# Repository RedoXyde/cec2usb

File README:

CEC to USB adapter, with HDMI passthrough

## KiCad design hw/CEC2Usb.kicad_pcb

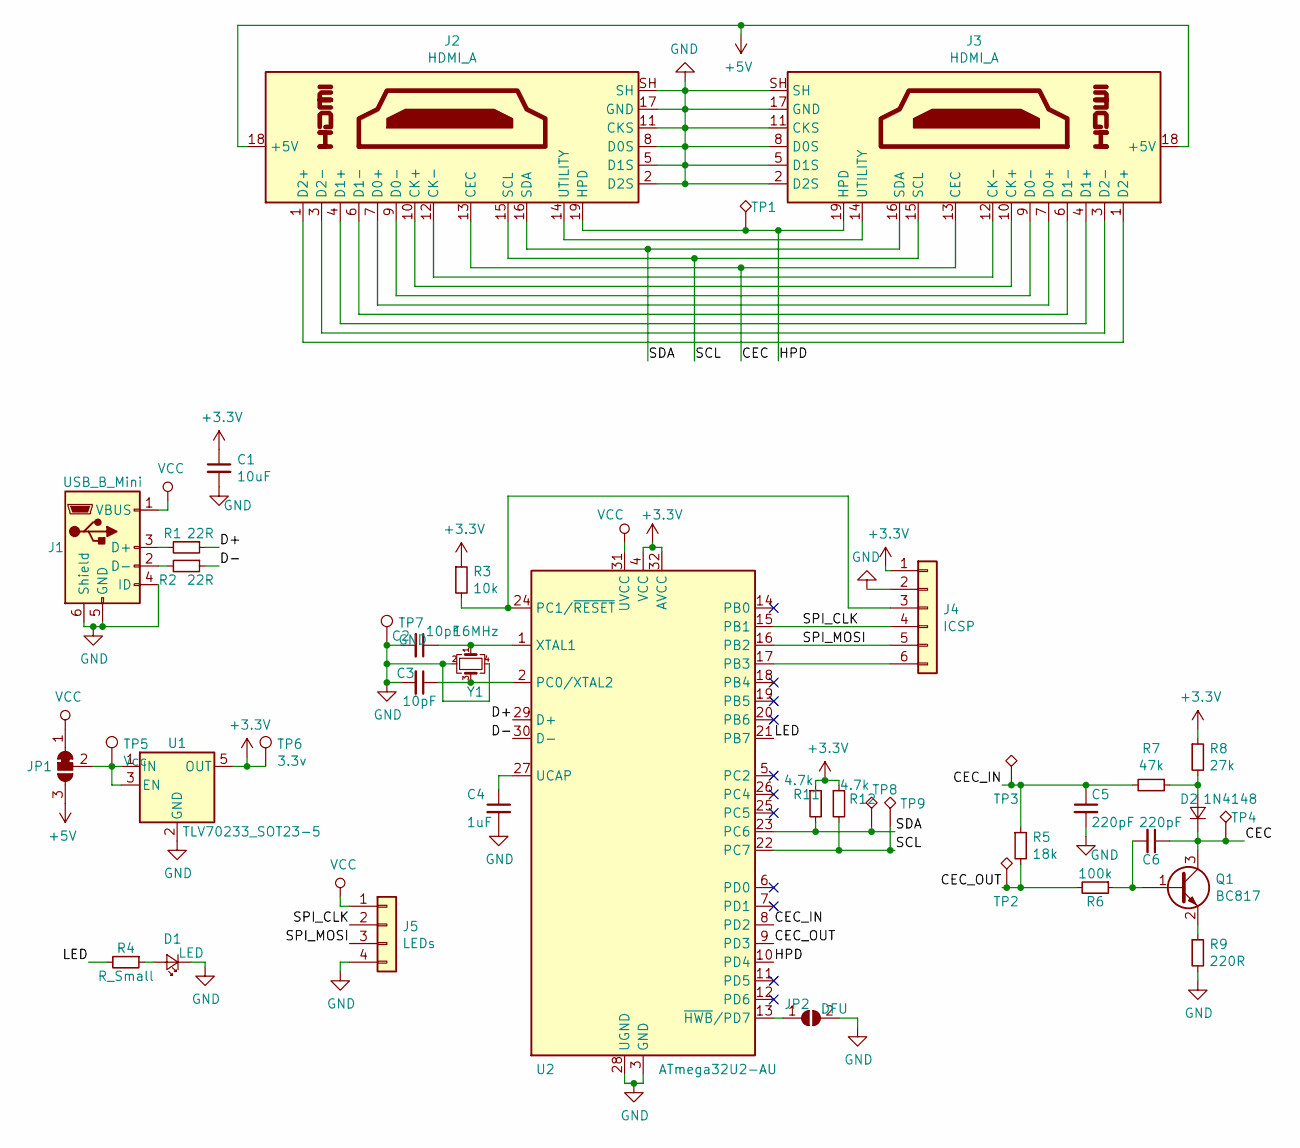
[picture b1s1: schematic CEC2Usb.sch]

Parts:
C1: 10uF; C_0603_1608Metric
C2, C3: 10pF; C_0603_1608Metric
C4: 1uF; C_0603_1608Metric
C5, C6: 220pF; C_0603_1608Metric
D1: LED; LED_0603_1608Metric_Pad1.05x0.95mm_HandSolder
D2: 1N4148; D_SOD-123
J1: USB_B_Mini; USB_Mini-B_Lumberg_2486_01_Horizontal
J2: HDMI_A; HDMI-19P-SND13x
J3: HDMI_A; HDMI-19P-SNDx
J4: ICSP; PinHeader_1x06_P1.27mm_Vertical
J5: LEDs; PinHeader_1x04_P2.54mm_Vertical
JP1: SolderJumper_3_Bridged12; SolderJumper-3_P1.3mm_Bridged12_RoundedPad1.0x1.5mm
JP2: DFU; SolderJumper-2_P1.3mm_Open_RoundedPad1.0x1.5mm
Q1: BC817; SOT-23
R1, R2: 22R; R_0603_1608Metric_Pad1.05x0.95mm_HandSolder
R3: 10k; R_0603_1608Metric_Pad1.05x0.95mm_HandSolder
R4: R_Small; R_0603_1608Metric_Pad1.05x0.95mm_HandSolder
R5: 18k; R_0603_1608Metric_Pad1.05x0.95mm_HandSolder
R6: 100k; R_0603_1608Metric_Pad1.05x0.95mm_HandSolder
R7: 47k; R_0603_1608Metric_Pad1.05x0.95mm_HandSolder
R8: 27k; R_0603_1608Metric_Pad1.05x0.95mm_HandSolder
R9: 220R; R_0603_1608Metric_Pad1.05x0.95mm_HandSolder
R11, R12: 4.7k; R_0603_1608Metric_Pad1.05x0.95mm_HandSolder
TP1: HPD; TestPoint_Pad_1.5x1.5mm
TP2: CEC_OUT; TestPoint_Pad_1.5x1.5mm
TP3: CEC_IN; TestPoint_Pad_1.5x1.5mm
TP4: CEC; TestPoint_Pad_1.5x1.5mm
TP5: Vcc; TestPoint_Pad_1.5x1.5mm
TP6: 3.3v; TestPoint_Pad_1.5x1.5mm
TP7: GND; TestPoint_Pad_1.5x1.5mm
TP8: SDA; TestPoint_Pad_1.5x1.5mm
TP9: SCL; TestPoint_Pad_1.5x1.5mm
U1: TLV70233_SOT23-5; SOT-23-5
U2: ATmega32U2-AU; TQFP-32_7x7mm_P0.8mm
Y1: 16MHz; Crystal_SMD_3225-4Pin_3.2x2.5mm

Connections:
+3V3: C1.1, J4.1, R3.1, R8.1, R11.1, R12.1, TP6.1, U1.5 (OUT), U2.4 (VCC), U2.32 (AVCC)
+5V: J2.18 (+5V), J3.18 (+5V), JP1.3 (B); also elsewhere on the board
/CEC: C6.1, D2.1 (K), J2.13 (CEC), J3.13 (CEC), Q1.3 (C), TP4.1
/CEC_IN: C5.1, R5.1, R7.2, TP3.1, U2.8 (PD2)
/CEC_OUT: R5.2, R6.2, TP2.1, U2.9 (PD3)
/D+: R1.1, U2.29 (D+)
/D-: R2.1, U2.30 (D-)
/HPD: J2.19 (HPD), J3.19 (HPD), TP1.1, U2.10 (PD4)
/LED: R4.2, U2.21 (PB7)
/SCL: J2.15 (SCL), J3.15 (SCL), R12.2, TP9.1, U2.22 (PC7)
/SDA: J2.16 (SDA), J3.16 (SDA), R11.2, TP8.1, U2.23 (PC6)
/SPI_CLK: J4.4, J5.2, U2.15 (PB1); also elsewhere on the board
/SPI_MOSI: J4.5, J5.3, U2.16 (PB2); also elsewhere on the board
GND: C1.2, C2.2, C3.2, C4.2, C5.2, D1.1 (K), J1.4 (ID), J1.5 (GND), J1.6 (Shield), J2.2 (D2S), J2.5 (D1S), J2.8 (D0S), J2.11 (CKS), J2.17 (GND), J2.SH, J3.2 (D2S), J3.5 (D1S), J3.8 (D0S), J3.11 (CKS), J3.17 (GND), J3.SH, J4.2, J5.4, JP2.2 (B), R9.2, TP7.1, U1.2 (GND), U2.3 (GND), U2.28 (UGND), Y1.2, Y1.4; also elsewhere on the board
unnamed: C2.1, U2.1 (XTAL1), Y1.1
unnamed: C3.1, U2.2 (PC0/XTAL2), Y1.3
unnamed: C4.1, U2.27 (UCAP)
unnamed: C6.2, Q1.1 (B), R6.1
unnamed: D1.2 (A), R4.1
unnamed: D2.2 (A), R7.1, R8.2
unnamed: J1.2 (D-), R2.2
unnamed: J1.3 (D+), R1.2
unnamed: J2.1 (D2+), J3.1 (D2+)
unnamed: J2.3 (D2-), J3.3 (D2-)
unnamed: J2.4 (D1+), J3.4 (D1+)
unnamed: J2.6 (D1-), J3.6 (D1-)
unnamed: J2.7 (D0+), J3.7 (D0+)
unnamed: J2.9 (D0-), J3.9 (D0-)
unnamed: J2.10 (CK+), J3.10 (CK+)
unnamed: J2.12 (CK-), J3.12 (CK-)
unnamed: J2.14 (UTILITY), J3.14 (UTILITY)
unnamed 31: J4.3, R3.2, U2.24 (PC1/~RESET); also elsewhere on the board
unnamed: J4.6, U2.17 (PB3)
unnamed 33: JP1.2 (C), TP5.1, U1.1 (IN), U1.3 (EN); also elsewhere on the board
unnamed: JP2.1 (A), U2.13 (~HWB~/PD7)
unnamed: Q1.2 (E), R9.1
VCC: J1.1 (VBUS), J5.1, JP1.1 (A), U2.31 (UVCC); also elsewhere on the board

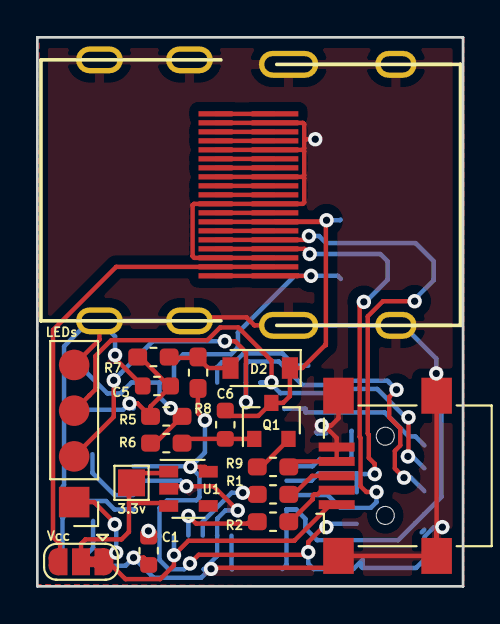
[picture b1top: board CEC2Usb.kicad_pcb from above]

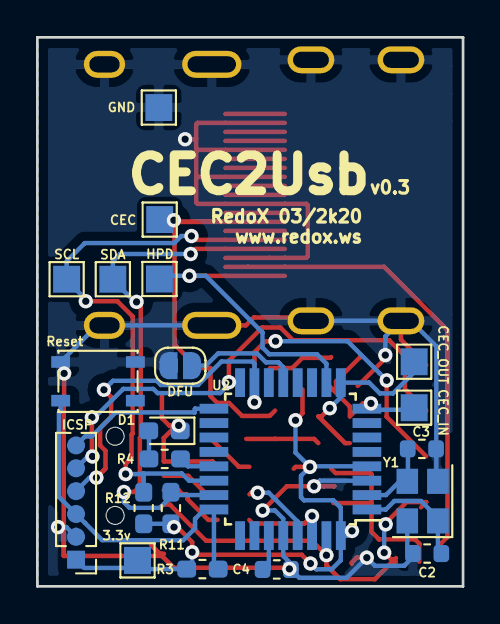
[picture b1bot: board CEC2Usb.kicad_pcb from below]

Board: 2 copper layers, 23.7 x 30.5 mm, 40 parts (21 on the bottom side), 37 nets.

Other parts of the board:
3.3v: Vcc; TestPoint_Pad_1.5x1.5mm
LEDs: LEDs; PinHeader_1x04_P2.54mm_Vertical
Reset: SW_SPST_PTS810
Vcc: SolderJumper_3_Bridged12; SolderJumper-3_P1.3mm_Bridged12_RoundedPad1.0x1.5mm

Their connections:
+5V: Vcc.3; also elsewhere on the board
/SPI_CLK: LEDs.2; also elsewhere on the board
/SPI_MOSI: LEDs.3; also elsewhere on the board
GND: LEDs.4, Reset.2; also elsewhere on the board
unnamed 31: Reset.1; also elsewhere on the board
unnamed 33: 3.3v.1, Vcc.2; also elsewhere on the board
VCC: LEDs.1, Vcc.1; also elsewhere on the board

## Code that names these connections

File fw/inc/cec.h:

/*
MIT License

Copyright (c) 2019 RedoX

Permission is hereby granted, free of charge, to any person obtaining a copy
of this software and associated documentation files (the "Software"), to deal
in the Software without restriction, including without limitation the rights
to use, copy, modify, merge, publish, distribute, sublicense, and/or sell
copies of the Software, and to permit persons to whom the Software is
furnished to do so, subject to the following conditions:

The above copyright notice and this permission notice shall be included in all
copies or substantial portions of the Software.

THE SOFTWARE IS PROVIDED "AS IS", WITHOUT WARRANTY OF ANY KIND, EXPRESS OR
IMPLIED, INCLUDING BUT NOT LIMITED TO THE WARRANTIES OF MERCHANTABILITY,
FITNESS FOR A PARTICULAR PURPOSE AND NONINFRINGEMENT. IN NO EVENT SHALL THE
AUTHORS OR COPYRIGHT HOLDERS BE LIABLE FOR ANY CLAIM, DAMAGES OR OTHER
LIABILITY, WHETHER IN AN ACTION OF CONTRACT, TORT OR OTHERWISE, ARISING FROM,
OUT OF OR IN CONNECTION WITH THE SOFTWARE OR THE USE OR OTHER DEALINGS IN THE
SOFTWARE.
*/

#ifndef _CEC_H_
#define _CEC_H_

#include <stdint.h>

#define CEC_IN  PD2 // INT2n, AIN1, RXD1
#define CEC_OUT PD3 // INT3n, TXD1
#define HDP     PD4 // INT5

#define CEC_ADDR_BROADCAST 0xF
#define CEC_TX_MAX_TRIES     6

#define CEC_DEFAULT           0x00
#define CEC_LISTEN_ONLY       0x01
#define CEC_PROMISCUIOUS      0x02
#define CEC_ALLOW_ALL_OPCODES 0x04

#define CEC_HWADDR_LEN 4

void CEC_Init(void);
void CEC_setMode(const uint8_t m);
void CEC_setHWAddr(const uint8_t addr[CEC_HWADDR_LEN]);
int8_t CEC_registerLogicalAddr(const uint8_t addr, const uint8_t skipPoll);

typedef void (*cec_cb)(const uint8_t st, const uint8_t* data, const uint8_t len);

void CEC_registerOpcode(const uint8_t opcode, cec_cb hdlr);
void CEC_setDefaultHandler(cec_cb hdlr);

void CEC_tx(const uint8_t* data, const uint8_t len, const uint8_t tries);
void CEC_processQueue(void);

#endif

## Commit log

2019-10-07 Add README
2019-10-07 [HW] Add HW v1.1
2019-10-07 [SW] Add base, does nothing yet
2019-10-07 [FW] Add current firmware, does RX and TX. No High level yet.
2019-10-07 Add .gitignore
2020-04-23 [Fw] Add "high level" functions, WIP
2020-04-23 [Fw] Add support for USB HID Feature report. Works better with vanilla Hyperion. Not tested IRL.
2020-04-23 [Fw] Update Tx, add per-msg tries number
2020-04-23 [Fw] Commit current (v0.2) .hex file
2020-04-23 [Fw] Add support for WS2812 LEDs. Hardcoded for 99 LEDs
2020-04-23 [HW] Minor rev to add reset button to witch to DFU
2020-04-23 [Fw] Add High level protocol.
2020-04-23 [Fw] Remove delay in main loop
2020-04-23 [Fw] Move handlers to a dedicated file to cleanup main
2020-04-23 [Fw] Don't queue <Polling Message>
2020-04-23 [Fw] Add DFU bootloader
2020-04-23 [Fw] Add Remote keys mapping
2020-04-23 [Fw] Add CEC_Protocol header with opcodes and keys definitions
2020-04-23 [Fw] Auto-allocate device address
2020-04-23 [FW] cec_cb also get ACK/NACK status now. Fixed first NACK on reply.Tweaked delays.
2020-04-23 [Fw] Cleanup and update for v0.2
2020-04-23 [Fw] Fix chmods
2020-04-23 [Hw] Fix silkscreen
2020-04-23 [Doc] Add schematic and assembly cheatsheet
2020-04-23 [Fw] Tweak CEC queues size, add isIdle
2020-04-23 [Fw] Map CEC Keys to USB Keyboard Keys for Kodi
2020-04-23 [Fw] Move everything CEC2Usb to subfolder
2020-04-23 [Fw] Fix usb numInterfaces
2020-04-23 [Hw] v0.2, Fixed mistakes, moved stuff, add LEDs conn
2020-04-23 [Fw] Import Software I2C lib from old project to read EDID (and get Physical Address)
2020-04-23 [Fw] CEC, cleanup, add addresses-related methods
2020-04-23 [Fw] Fi keyUp/down
2020-04-23 [Fw] Remove debug in main
2020-04-23 [Fw] Fix Logical address detection
2020-04-23 [Fw] Add Colored keys for LG remote
2020-04-23 [Fw] Add support for LG 0x0B command
2020-04-23 [Fw] Read EDID to get Physical address
2020-04-23 [Fw] Rework wait for physical address in main
2020-04-23 [Fw] Cleanup SoftI2C, remove End
2020-04-23 [Fw] Fix Edid Read
2020-04-23 [Fw] SoftI2C, return false if start fails
2020-04-23 [Fw] Add opcode handler for Samsung Anynet, based on libcec source. Untested, may not work at all
